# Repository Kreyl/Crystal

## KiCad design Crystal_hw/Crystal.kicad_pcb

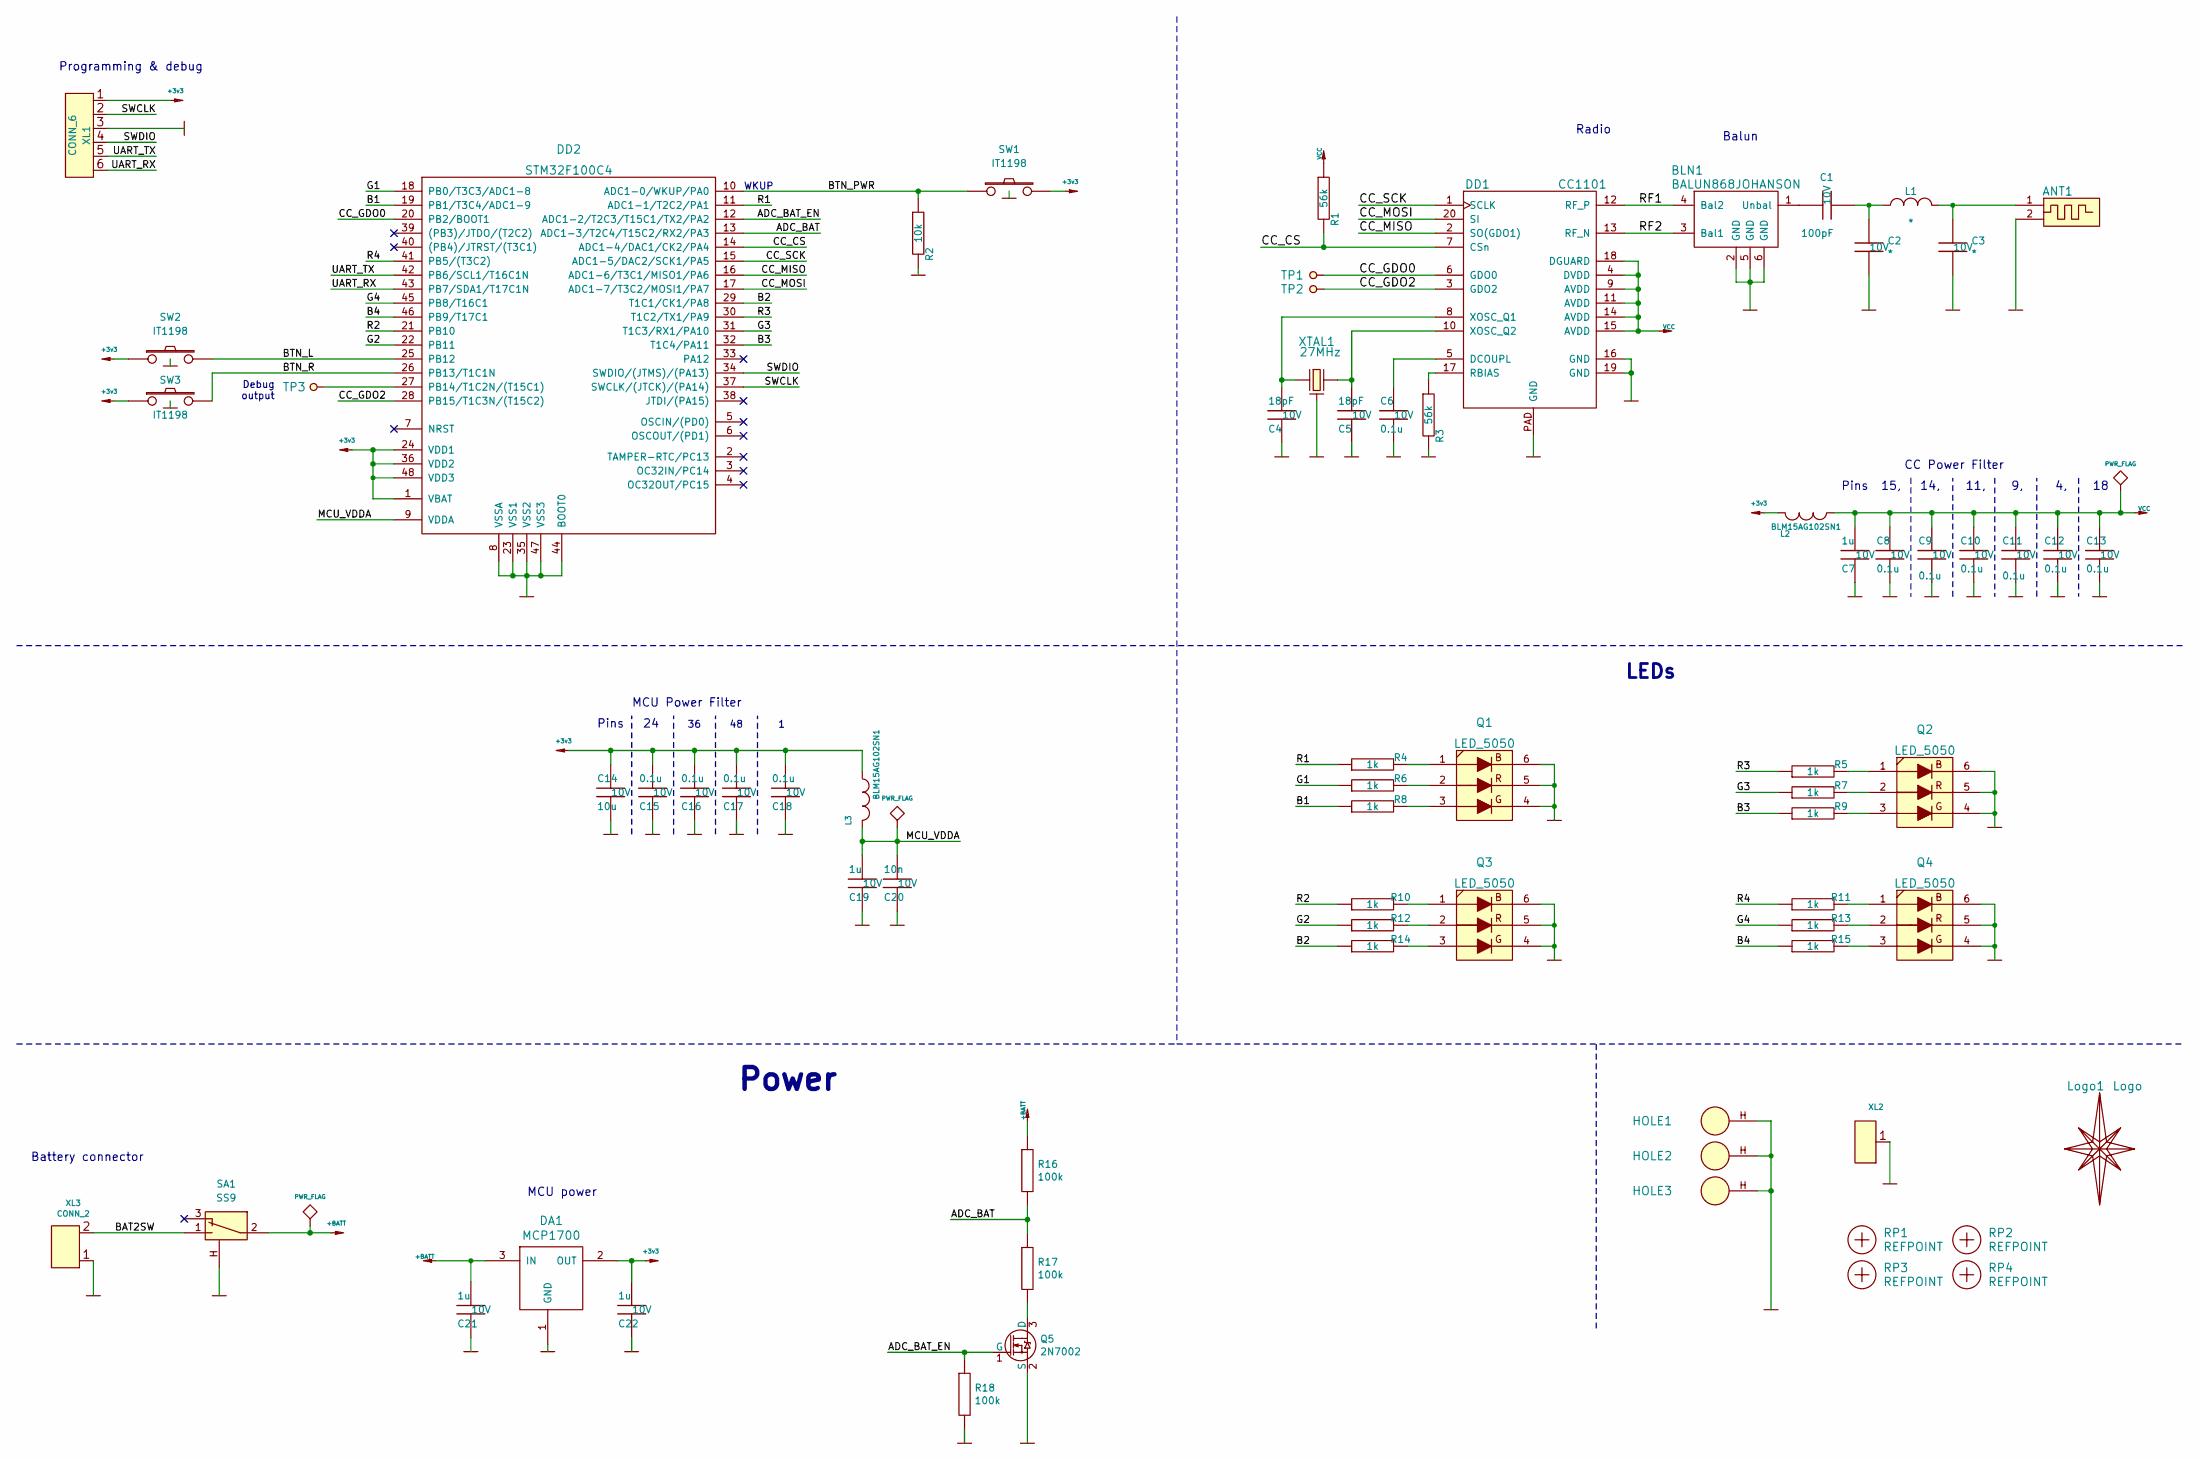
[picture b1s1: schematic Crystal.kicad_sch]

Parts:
ANT1: ANT_PCB_MONO_2PIN; Locket5_MIRR
BLN1: BALUN868JOHANSON; BALUN_JOHANSON868
C1: 100pF; CAP_0402; Tolerance 20%; Voltage 10V
C2, C3: *; CAP_0402; Tolerance 20%; Voltage 10V
C4, C5: 18pF; CAP_0603_Silks; Tolerance 20%; Voltage 10V
C6, C8, C9, C10, C11, C12, C13, C15, C16, C17, C18: 0.1u; CAP_0603_Silks; Tolerance 20%; Voltage 10V
C7, C19, C21, C22: 1u; CAP_0603_Silks; Tolerance 20%; Voltage 10V
C14: 10u; CAP_0603_Silks; Tolerance 20%; Voltage 10V
C20: 10n; CAP_0603_Silks; Tolerance 20%; Voltage 10V
DA1: MCP1700; SOT23-3A
DD1: CC1101; QFN20
DD2: STM32F100C4; LQFP48
HOLE1, HOLE2, HOLE3: HOLE_METALLED; Hole2d4_out4d4mm
L1: *; IND_0402; Tolerance 20%
L2, L3: BLM15AG102SN1; IND_0402; Tolerance 20%
Logo1: Logo; Ostranna_16d9_13d5
Q1, Q2, Q3, Q4: LED_5050
Q5: 2N7002; SOT23-3
R1, R3: 56k; RES_0603; Tolerance 1%
R2: 10k; RES_0603; Tolerance 1%
R4, R5, R6, R7, R8, R9, R10, R11, R12, R13, R14, R15: 1k; RES_0603; Tolerance 1%
R16, R17, R18: 100k; RES_0603; Tolerance 1%
RP1, RP2, RP3, RP4: REFPOINT; REF_POINT_1MM
SA1: SS9; SW_SS9
SW1, SW2, SW3: IT1198; BTN_IT1198
TP1, TP2, TP3: TESTPOINT; TESTPOINT_1MM
XL1: CONN_6; PLS-6_LOCK
XL2: CONN_1; PLS-1Square
XL3: CONN_2; SLD_2_2D5
XTAL1: 27MHz; 03225C4

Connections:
+3v3: C14.2, C15.1, C16.1, C17.1, C18.1, C22.1, DA1.2 (OUT), DD2.1 (VBAT), DD2.24 (VDD1), DD2.36 (VDD2), DD2.48 (VDD3), L2.2, L3.1, SW1.2, SW2.1, SW3.1, XL1.1
+BATT: C21.1, DA1.3 (IN), R16.1, SA1.2
/ADC_BAT: DD2.13 (ADC1-3/T2C4/T15C2/RX2/PA3), R16.2, R17.1
/ADC_BAT_EN: DD2.12 (ADC1-2/T2C3/T15C1/TX2/PA2), Q5.1 (G), R18.1
/B1: DD2.19 (PB1/T3C4/ADC1-9), R8.1
/B2: DD2.29 (T1C1/CK1/PA8), R14.1
/B3: DD2.32 (T1C4/PA11), R9.1
/B4: DD2.46 (PB9/T17C1), R15.1
/BAT2SW: SA1.1, XL3.2 (PM)
/BTN_L: DD2.25 (PB12), SW2.2
/BTN_PWR: DD2.10 (ADC1-0/WKUP/PA0), R2.1, SW1.1
/BTN_R: DD2.26 (PB13/T1C1N), SW3.2
/CC_CS: DD1.7 (CSn), DD2.14 (ADC1-4/DAC1/CK2/PA4), R1.2
/CC_GDO0: DD1.6 (GDO0), DD2.20 (PB2/BOOT1), TP1.1
/CC_GDO2: DD1.3 (GDO2), DD2.28 (PB15/T1C3N/(T15C2)), TP2.1
/CC_MISO: DD1.2 (SO(GDO1)), DD2.16 (ADC1-6/T3C1/MISO1/PA6)
/CC_MOSI: DD1.20 (SI), DD2.17 (ADC1-7/T3C2/MOSI1/PA7)
/CC_SCK: DD1.1 (SCLK), DD2.15 (ADC1-5/DAC2/SCK1/PA5)
/G1: DD2.18 (PB0/T3C3/ADC1-8), R6.1
/G2: DD2.22 (PB11), R12.1
/G3: DD2.31 (T1C3/RX1/PA10), R7.1
/G4: DD2.45 (PB8/T16C1), R13.1
/MCU_VDDA: C19.1, C20.1, DD2.9 (VDDA), L3.2
/R1: DD2.11 (ADC1-1/T2C2/PA1), R4.1
/R2: DD2.21 (PB10), R10.1
/R3: DD2.30 (T1C2/TX1/PA9), R5.1
/R4: DD2.41 (PB5/(T3C2)), R11.1
/RF1: BLN1.4 (Bal2), DD1.12 (RF_P)
/RF2: BLN1.3 (Bal1), DD1.13 (RF_N)
/SWCLK: DD2.37 (SWCLK/(JTCK)/(PA14)), XL1.2
/SWDIO: DD2.34 (SWDIO/(JTMS)/(PA13)), XL1.4
/UART_RX: DD2.43 (PB7/SDA1/T17C1N), XL1.6
/UART_TX: DD2.42 (PB6/SCL1/T16C1N), XL1.5
GND: ANT1.2, BLN1.2 (GND), BLN1.5 (GND), BLN1.6 (GND), C2.2, C3.2, C4.2, C5.2, C6.1, C7.2, C8.2, C9.2, C10.2, C11.2, C12.2, C13.2, C14.1, C15.2, C16.2, C17.2, C18.2, C19.2, C20.2, C21.2, C22.2, DA1.1 (GND), DD1.16 (GND), DD1.19 (GND), DD1.PAD (GND), DD2.8 (VSSA), DD2.23 (VSS1), DD2.35 (VSS2), DD2.44 (BOOT0), DD2.47 (VSS3), HOLE1.H, HOLE2.H, HOLE3.H, Q1.4 (B), Q1.5 (G), Q1.6, Q2.4 (B), Q2.5 (G), Q2.6, Q3.4 (B), Q3.5 (G), Q3.6, Q4.4 (B), Q4.5 (G), Q4.6, Q5.2 (S), R2.2, R3.2, R18.2, SA1.H, SW1.H, SW2.H, SW3.H, XL1.3, XL2.1, XL3.1, XTAL1.H
unnamed: ANT1.1, C3.1, L1.2
unnamed: BLN1.1 (Unbal), C1.1
unnamed: C1.2, C2.1, L1.1
unnamed: C4.1, DD1.8 (XOSC_Q1), XTAL1.1
unnamed: C5.1, DD1.10 (XOSC_Q2), XTAL1.2
unnamed: C6.2, DD1.5 (DCOUPL)
unnamed: DD1.17 (RBIAS), R3.1
unnamed: DD2.27 (PB14/T1C2N/(T15C1)), TP3.1
unnamed: Q1.1, R4.2
unnamed: Q1.2, R6.2
unnamed: Q1.3, R8.2
unnamed: Q2.1, R5.2
unnamed: Q2.2, R7.2
unnamed: Q2.3, R9.2
unnamed: Q3.1, R10.2
unnamed: Q3.2, R12.2
unnamed: Q3.3, R14.2
unnamed: Q4.1, R11.2
unnamed: Q4.2, R13.2
unnamed: Q4.3, R15.2
unnamed: Q5.3 (D), R17.2
VCC: C7.1, C8.1, C9.1, C10.1, C11.1, C12.1, C13.1, DD1.4 (DVDD), DD1.9 (AVDD), DD1.11 (AVDD), DD1.14 (AVDD), DD1.15 (AVDD), DD1.18 (DGUARD), L2.1, R1.1

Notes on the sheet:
WKUP
CC Power Filter
Pins
Balun
Power
MCU power
Debug output
Battery connector
Radio
LEDs
Programming & debug
MCU Power Filter
Pins 15, 14, 11, 9, 4, 18

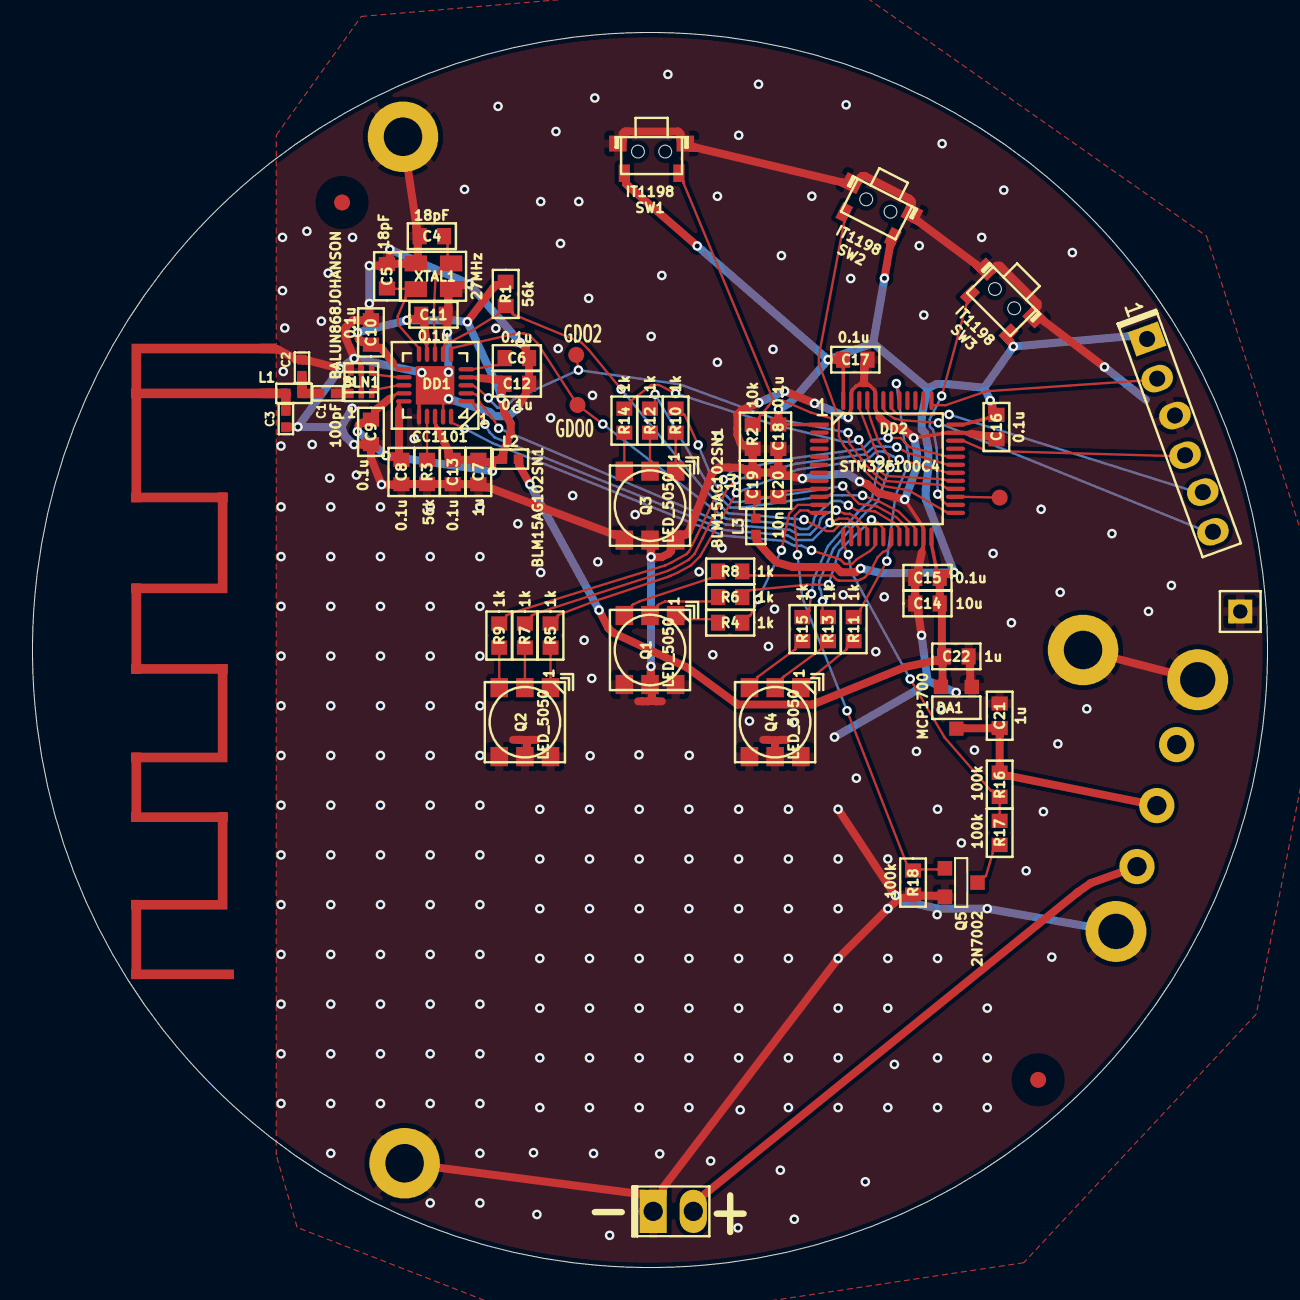
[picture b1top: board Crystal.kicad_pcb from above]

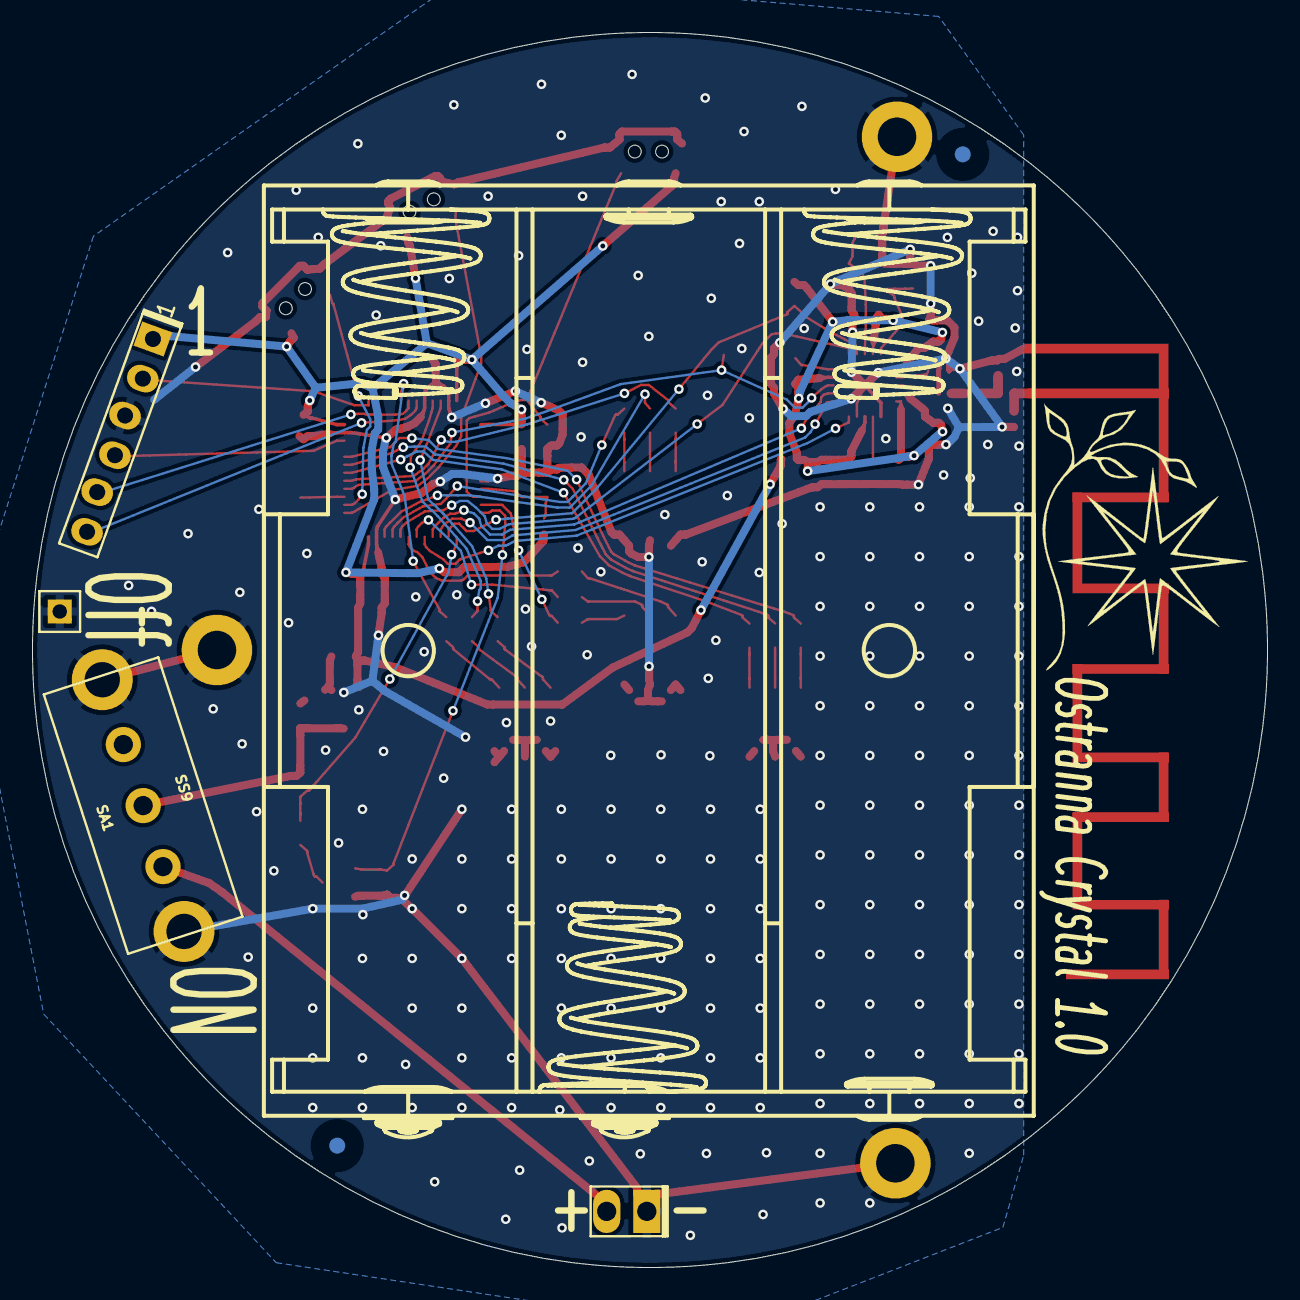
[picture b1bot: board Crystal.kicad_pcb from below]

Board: 2 copper layers, 77.0 x 77.0 mm, 72 parts (5 on the bottom side), 56 nets.

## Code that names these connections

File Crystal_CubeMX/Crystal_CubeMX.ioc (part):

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Mcu.Name=STM32F100C(4-6)Tx
Mcu.Package=LQFP48
Mcu.UserName=STM32F100C4Tx
PA0-WKUP.Mode=SYS_WakeUp0
PA0-WKUP.Signal=SYS_WKUP
PA1.Signal=S_TIM2_CH2
PA10.Signal=S_TIM1_CH3
PA11.Signal=S_TIM1_CH4
PA13.Mode=JTAG_5_pins
PA13.Signal=SYS_JTMS-SWDIO
PA14.Mode=JTAG_5_pins
PA14.Signal=SYS_JTCK-SWCLK
PA15.Mode=JTAG_5_pins
PA15.Signal=SYS_JTDI
PA2.Signal=GPIO_Output
PA3.Signal=ADCx_IN3
PA4.Signal=GPIO_Input
PA5.Mode=Full_Duplex_Master
PA5.Signal=SPI1_SCK
PA6.Mode=Full_Duplex_Master
PA6.Signal=SPI1_MISO
PA7.Mode=Full_Duplex_Master
PA7.Signal=SPI1_MOSI
PA8.Signal=S_TIM1_CH1
PA9.Signal=S_TIM1_CH2
PB0.Signal=S_TIM3_CH3
PB1.Signal=S_TIM3_CH4
PB10.Signal=S_TIM2_CH3
PB11.Signal=S_TIM2_CH4
PB14.Signal=S_TIM15_CH1
PB15.Signal=S_TIM15_CH2
PB2.Signal=GPIO_Output
PB3.Mode=JTAG_5_pins
PB3.Signal=SYS_JTDO-TRACESWO
PB4.Mode=JTAG_5_pins
PB4.Signal=SYS_NJTRST
PB5.Signal=S_TIM3_CH2
PB6.Mode=Asynchronous
PB6.Signal=USART1_TX
PB7.Mode=Asynchronous
PB7.Signal=USART1_RX
PB8.Signal=S_TIM16_CH1
PB9.Signal=S_TIM17_CH1
board=custom

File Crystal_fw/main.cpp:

#if 1 // ============================ Includes =================================
#include "hal.h"
#include "MsgQ.h"
#include "uart.h"
#include "shell.h"
#include "CrystalLed.h"
#include "ChunkTypes.h"
#include "buttons.h"
#include "SaveToFlash.h"
#include "adc_f100.h"
#include "battery_consts.h"
#include "radio_lvl1.h"
#endif
#if 1 // ======================== Variables & prototypes =======================
// Forever
bool OsIsInitialized = false;
EvtMsgQ_t<EvtMsg_t, MAIN_EVT_Q_LEN> EvtQMain;
static const UartParams_t CmdUartParams(115200, CMD_UART_PARAMS);
CmdUart_t Uart{&CmdUartParams};
void OnCmd(Shell_t *PShell);
void ITask();

extern Adc_t Adc;
void OnMeasurementDone();

static const uint32_t kEffCnt = 2;

const EffSettings eff_settings[kEffCnt] = {
     //  Off     On       Smooth     Color1 H    Color2 H
        {9, 45,  99,  99,  108, 810,    0,   2,   359, 360}, // 0 Red
        {7, 18,  45, 180,  720, 999,   80, 160,   200, 260}, // 1 Green&Blue
        /*
        {9, 45,  9, 54,   108, 360,   330, 360,   215, 230}, // 0 Requiem
        {9, 45,  9, 54,   108, 360,     0,  15,   250, 270}, // 2 tango
        {9, 45,  9, 54,   405, 630,    80, 160,   260, 290}, // 3 waltz
        {9, 45, 99, 99,   108, 630,   225, 250,   250, 265}, // 5 dance
        {9, 45,  9, 54,   270, 405,   120, 270,    50,  77}, // 6
        */
};

const EffSettings *pcurr_settings = &eff_settings[1];

TmrKL_t TmrOneS {TIME_MS2I(999), evtIdEverySecond, tktPeriodic};
#endif

void main(void) {
#if 0 // ==== Get source of wakeup ====
    rccEnablePWRInterface(FALSE);
    if(PWR->CSR & PWR_CSR_WUF) { // Wakeup occured
        // Is it button?
        PinSetupInput(BTN1_PIN, pudPullDown);
        if(Btn1IsPressed()) {
            // Check if pressed long enough
            for(uint32_t i=0; i<540000; i++) {
                // Go sleep if btn released too fast
                if(!Btn1IsPressed()) EnterSleepNow();
            }
            // Btn was keeped in pressed state long enough, proceed with powerOn
        }
    }
#endif

#if 1 // ==== Iwdg, Clk, Os, EvtQ, Uart ====
    // Start Watchdog. Will reset in main thread by periodic 1 sec events.
    Iwdg::InitAndStart(4500);
    Iwdg::DisableInDebug();
    Clk.UpdateFreqValues();
    // Init OS
    halInit();
    chSysInit();
    OsIsInitialized = true;
    EvtQMain.Init();
#endif

    // ==== Init hardware ====
    Uart.Init();
    // Remap pins: disable JTAG leaving SWD, T3C2 at PB5, T2C3&4 at PB10&11, USART1 at PB6/7
    AFIO->MAPR = (0b010UL << 24) | (0b10UL << 10) | (0b10UL << 8) | AFIO_MAPR_USART1_REMAP;
    // Power-on, or radio pkt received => proceed with init
    Printf("\r%S %S\r", APP_NAME, XSTRINGIFY(BUILD_TIME));
    Clk.PrintFreqs();

    // LEDs
    CrystalLeds::Init();
    CrystalLeds::On();
    SimpleSensors::Init(); // Buttons

    // Battery measurement
    PinSetupAnalog(ADC_BAT_PIN);
    PinSetupOut(ADC_BAT_EN, omPushPull);
    PinSetHi(ADC_BAT_EN);
    Adc.Init();

    Radio.Init();
    TmrOneS.StartOrRestart();

    // Main cycle
    ITask();
}

__noreturn
void ITask() {
    while(true) {
        EvtMsg_t Msg = EvtQMain.Fetch(TIME_INFINITE);
        switch(Msg.ID) {
            case evtIdShellCmd:
                OnCmd((Shell_t*)Msg.Ptr);
                ((Shell_t*)Msg.Ptr)->SignalCmdProcessed();
                break;

            case evtIdButtons:
                Printf("Btn %u %u\r", Msg.BtnEvtInfo.BtnID, Msg.BtnEvtInfo.Type);
                if(Msg.BtnEvtInfo.BtnID == 0) {
                    Adc.StartMeasurement();
                }
                break;

            case evtIdRadioCmd:
                Printf("RCmd: %u\r", Msg.Value);
                CrystalLeds::On();
                if(Msg.Value == 0) pcurr_settings = &eff_settings[0];
                else pcurr_settings = &eff_settings[1];
                break;

            case evtIdEverySecond:
//                Printf("Second\r");
                Iwdg::Reload();
                break;

            case evtIdAdcRslt:
                OnMeasurementDone();
                break;

            default: break;
        } // switch
    } // while true
}

void OnMeasurementDone() {
//    Printf("%u %u %u\r", Adc.GetResult(0), Adc.GetResult(1), Adc.Adc2mV(Adc.GetResult(0), Adc.GetResult(1)));
    // Calculate voltage
    uint32_t VBat = 2 * Adc.Adc2mV(Adc.GetResult(0), Adc.GetResult(1)); // *2 because of resistor divider
    uint8_t Percent = mV2PercentAlkaline(VBat);
    Printf("VBat: %umV; Percent: %u\r", VBat, Percent);
    ColorHSV_t hsv;
    if     (Percent <= 20) hsv = {0,   100, 100};
    else if(Percent <  80) hsv = {30,  100, 100};
    else                   hsv = {120, 100, 100};
    CrystalLeds::SetAllHsv(hsv);
    chThdSleepMilliseconds(1530);
    CrystalLeds::On();
}

#if 1 // ======================= Command processing ============================
void OnCmd(Shell_t *PShell) {
	Cmd_t *PCmd = &PShell->Cmd;
    // Handle command
    if(PCmd->NameIs("Ping")) PShell->Ok();
    else if(PCmd->NameIs("Version")) PShell->Print("%S %S\r", APP_NAME, XSTRINGIFY(BUILD_TIME));

    else PShell->CmdUnknown();
}
#endif

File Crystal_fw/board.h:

/*
 * board.h
 *
 *  Created on: 05 08 2018
 *      Author: Kreyl
 */

#ifndef BOARD_H__
#define BOARD_H__

// ==== General ====
#define APP_NAME            "Red&Green"

#ifndef TRUE
#define TRUE    1
#endif
#ifndef FALSE
#define FALSE   0
#endif

// Version of PCB
#define PCB_VER                 1

// MCU type as defined in the ST header.
#define STM32F100xB

// Freq of external crystal if any. Leave it here even if not used.
#define CRYSTAL_FREQ_HZ         12000000
#define LSI_FREQ_HZ             40000 // See datasheet

// OS timer settings
#define STM32_ST_IRQ_PRIORITY   2
#define STM32_ST_USE_TIMER      15
#define SYS_TIM_CLK             (Clk.APB2FreqHz)    // Timer 15 is clocked by APB2

//  Periphery
#define I2C1_ENABLED            FALSE
#define SIMPLESENSORS_ENABLED   TRUE
#define BUTTONS_ENABLED         TRUE

#define ADC_REQUIRED            TRUE
#define STM32_DMA_REQUIRED      TRUE    // Leave this macro name for OS

#if 1 // ========================== GPIO =======================================
// EXTI
#define INDIVIDUAL_EXTI_IRQ_REQUIRED    FALSE

// Buttons
#define BTN1_PIN        GPIOA,  0
#define BTN2_PIN        GPIOB, 12, pudPullDown
#define BTN3_PIN        GPIOB, 13, pudPullDown

// LEDs
#define LED1_R          { GPIOB,  0,  TIM3, 3, invNotInverted, omPushPull, 255 }
#define LED1_G          { GPIOB,  1,  TIM3, 4, invNotInverted, omPushPull, 255 }
#define LED1_B          { GPIOA,  1,  TIM2, 2, invNotInverted, omPushPull, 255 }

#define LED2_R          { GPIOB, 11,  TIM2, 4, invNotInverted, omPushPull, 255 }
#define LED2_G          { GPIOA,  8,  TIM1, 1, invNotInverted, omPushPull, 255 }
#define LED2_B          { GPIOB, 10,  TIM2, 3, invNotInverted, omPushPull, 255 }

#define LED3_R          { GPIOA, 10,  TIM1, 3, invNotInverted, omPushPull, 255 }
#define LED3_G          { GPIOA, 11,  TIM1, 4, invNotInverted, omPushPull, 255 }
#define LED3_B          { GPIOA,  9,  TIM1, 2, invNotInverted, omPushPull, 255 }

#define LED4_R          { GPIOB,  8, TIM16, 1, invNotInverted, omPushPull, 255 }
#define LED4_G          { GPIOB,  9, TIM17, 1, invNotInverted, omPushPull, 255 }
#define LED4_B          { GPIOB,  5,  TIM3, 2, invNotInverted, omPushPull, 255 }

// ADC
#define ADC_BAT_EN      GPIOA, 2
#define ADC_BAT_PIN     GPIOA, 3

// UART
#define UART_GPIO       GPIOB
#define UART_TX_PIN     6
#define UART_RX_PIN     7

// Radio: SPI, PGpio, Sck, Miso, Mosi, Cs, Gdo0
#define CC_Setup0       SPI1, GPIOA, 5,6,7, GPIOA,4, GPIOB,2

#endif // GPIO

#if 1 // =========================== I2C =======================================
// i2cclkPCLK1, i2cclkSYSCLK, i2cclkHSI
#define I2C_CLK_SRC     i2cclkHSI
#define I2C_BAUDRATE_HZ 400000
#endif

#if ADC_REQUIRED // ======================= Inner ADC ==========================
// Clock divider: clock is generated from the APB2
#define ADC_CLK_DIVIDER		adcDiv2

// ADC channels
#define ADC_BATTERY_CHNL 	3
#define ADC_VREFINT_CHNL    17 // const, see RefMan p.161
#define ADC_CHANNELS        { ADC_BATTERY_CHNL, ADC_VREFINT_CHNL }
#define ADC_CHANNEL_CNT     2   // Do not use countof(AdcChannels) as preprocessor does not know what is countof => cannot check
#define ADC_SAMPLE_TIME     ADC_SampleTime_55_5Cycles
#define ADC_SAMPLE_CNT      8   // How many times to measure every channel
#define ADC_SEQ_LEN         (ADC_SAMPLE_CNT * ADC_CHANNEL_CNT)
#endif

#if 1 // =========================== DMA =======================================
// ==== Uart ====
// Remap is made automatically if required
#define UART_DMA_TX     STM32_DMA_STREAM_ID(1, 4)
#define UART_DMA_RX     STM32_DMA_STREAM_ID(1, 5)
#define UART_DMA_CHNL   0 // dummy
#define UART_DMA_TX_MODE(Chnl) (STM32_DMA_CR_CHSEL(Chnl) | DMA_PRIORITY_LOW | STM32_DMA_CR_MSIZE_BYTE | STM32_DMA_CR_PSIZE_BYTE | STM32_DMA_CR_MINC | STM32_DMA_CR_DIR_M2P | STM32_DMA_CR_TCIE)
#define UART_DMA_RX_MODE(Chnl) (STM32_DMA_CR_CHSEL(Chnl) | DMA_PRIORITY_MEDIUM | STM32_DMA_CR_MSIZE_BYTE | STM32_DMA_CR_PSIZE_BYTE | STM32_DMA_CR_MINC | STM32_DMA_CR_DIR_P2M | STM32_DMA_CR_CIRC)

#if ADC_REQUIRED
#define ADC_DMA         STM32_DMA_STREAM_ID(1, 1)
#define ADC_DMA_MODE    STM32_DMA_CR_CHSEL(0) |   /* dummy */ \
                        DMA_PRIORITY_LOW | \
                        STM32_DMA_CR_MSIZE_HWORD | \
                        STM32_DMA_CR_PSIZE_HWORD | \
                        STM32_DMA_CR_MINC |       /* Memory pointer increase */ \
                        STM32_DMA_CR_DIR_P2M |    /* Direction is peripheral to memory */ \
                        STM32_DMA_CR_TCIE         /* Enable Transmission Complete IRQ */
#endif // ADC


#endif // DMA

#if 1 // ========================== USART ======================================
#define PRINTF_FLOAT_EN FALSE
#define UART_TXBUF_SZ   128
#define UART_RXBUF_SZ   84
#define CMD_BUF_SZ      64

#define CMD_UART        USART1

#define UARTS_CNT       1

#define CMD_UART_PARAMS \
    CMD_UART, UART_GPIO, UART_TX_PIN, UART_GPIO, UART_RX_PIN, \
    UART_DMA_TX, UART_DMA_RX, UART_DMA_TX_MODE(UART_DMA_CHNL), UART_DMA_RX_MODE(UART_DMA_CHNL)

#endif

#endif //BOARD_H__

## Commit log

2021-11-17 PCB layout started
2021-11-20 PCB is ready
2021-11-28 Printf works
2021-11-28 + LEDs mapped properly
2021-11-28 + Btns work
2021-11-28 + Saving/loading from Flash
2021-11-28 Smooth power-on
2021-11-28 + Battery meaasurement
2021-11-29 Fighting with PwrOff
2021-11-30 + Seems working * Switched to CrystalLed_t
2021-12-02 battery indication HSV tuned a little
2021-12-02 + Radio works
2021-12-03 Smooth transition when switching by radio
2022-02-05 + Antenna matched
2022-02-10 * Yellow switched to blue + hex file RC
2022-02-10 +hex
2022-02-10 + hex
2022-05-04 Release
2023-03-17 AppName changed
2023-04-18 Switch to Eclipse
2023-09-16 + Radio control works
2024-05-24 + BUILD TIME
2024-05-24 In progress
